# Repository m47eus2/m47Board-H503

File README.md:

# m47Board-H503

## Custom PCB designed for STM32H503
- STM32C031C6T6 MCU
- USB-C port with ESD protection
- SWD and DFU programming interfaces
- Goldpin headers for all GPIO pins
- User Button and User Led
- RST and BOOT0 buttons
- TLV1117LV33DCYR 3.3V 1A LDO

## PCB Renders

## Schematic

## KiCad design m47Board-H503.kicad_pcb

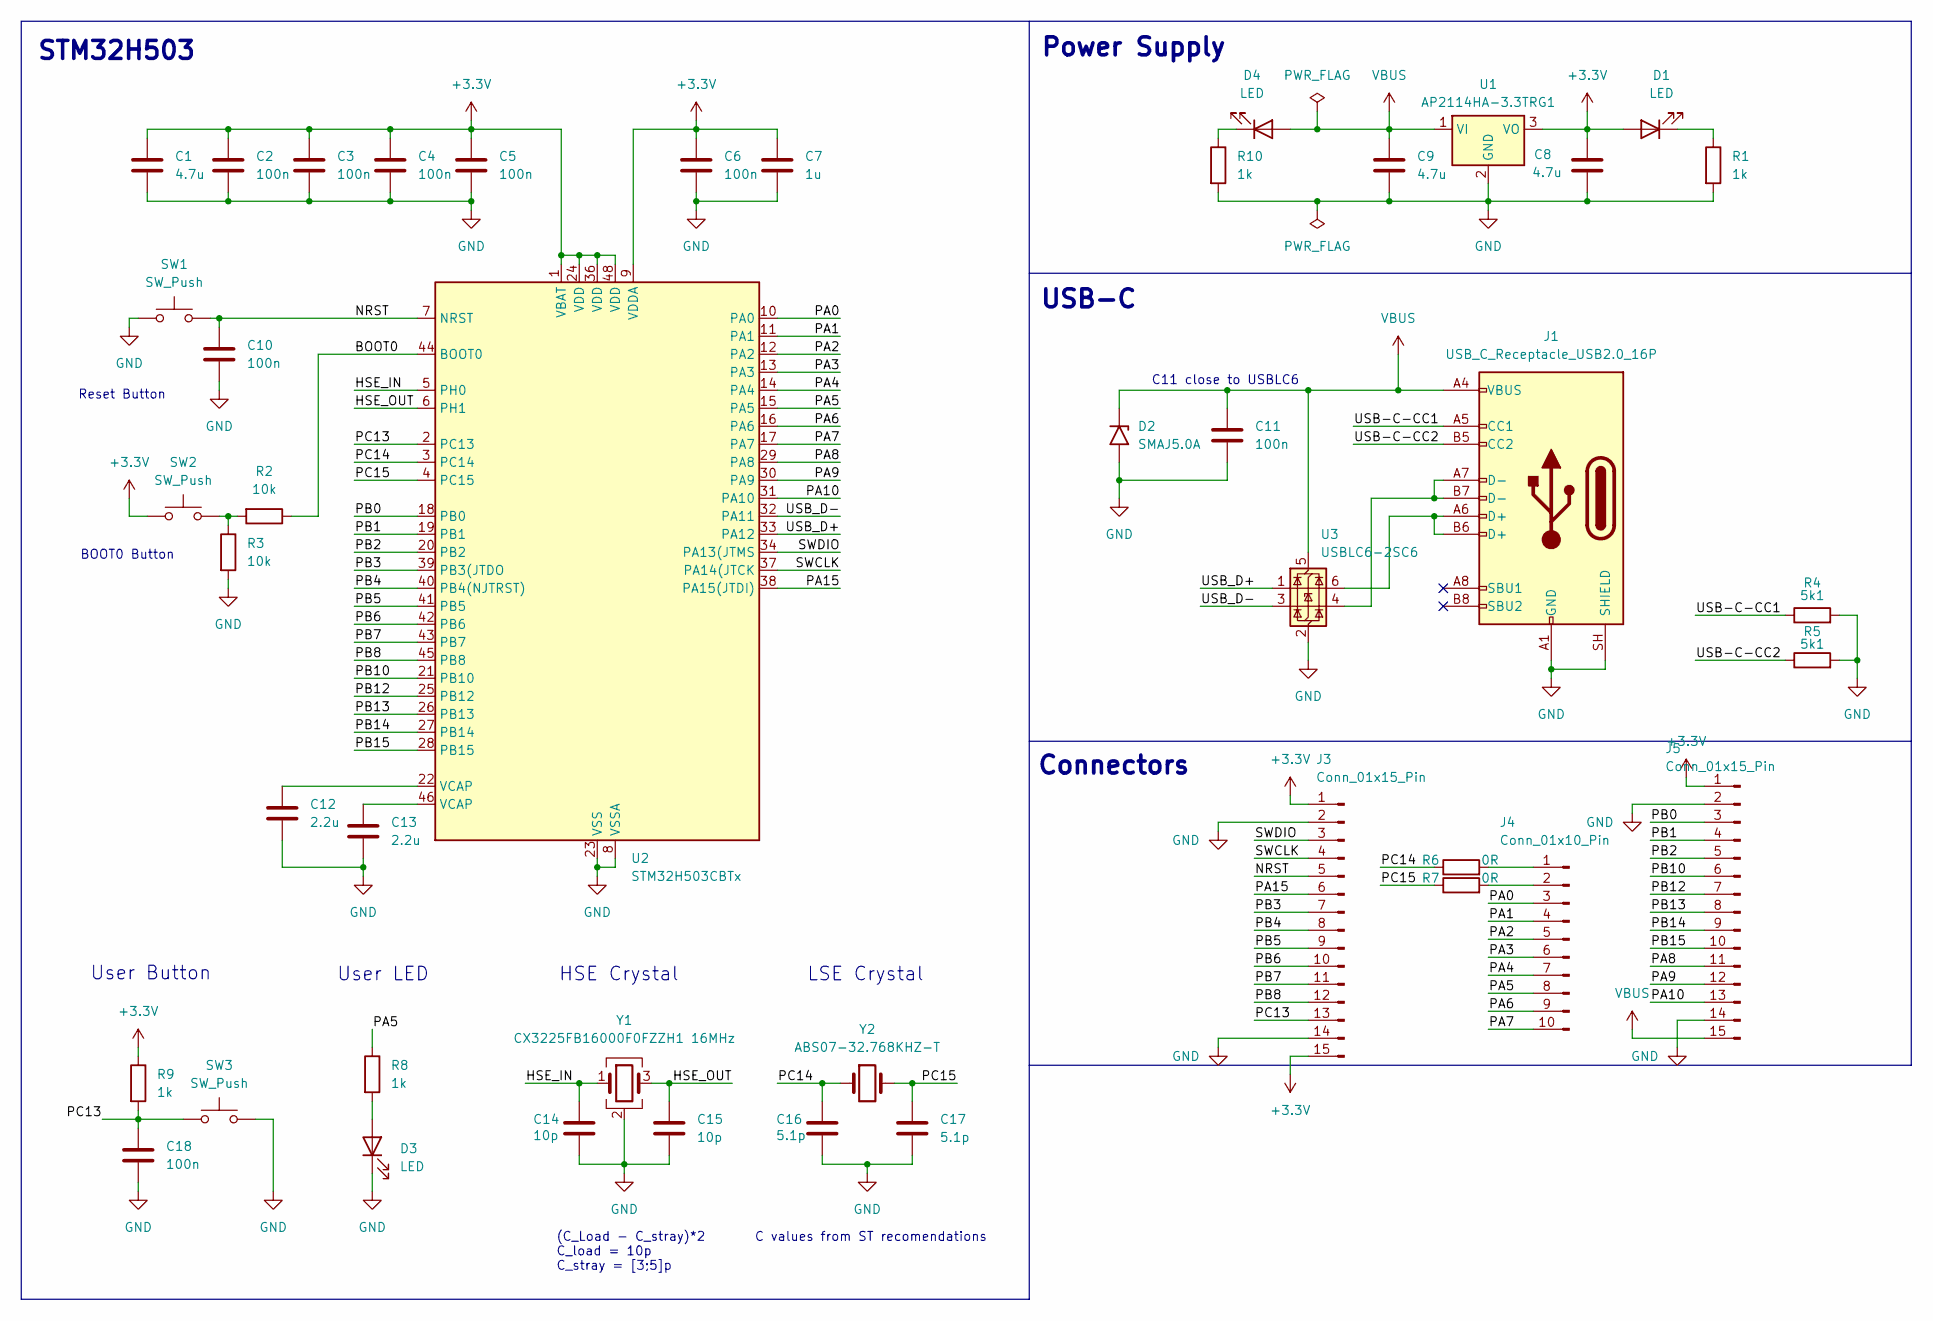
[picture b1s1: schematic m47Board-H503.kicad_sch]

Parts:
C1, C8, C9: 4.7u; C_0805_2012Metric_Pad1.18x1.45mm_HandSolder
C2, C3, C4, C5, C6, C10, C11, C18: 100n; C_0402_1005Metric_Pad0.74x0.62mm_HandSolder
C7: 1u; C_0603_1608Metric_Pad1.08x0.95mm_HandSolder
C12, C13: 2.2u; C_0603_1608Metric_Pad1.08x0.95mm_HandSolder
C14, C15: 10p; C_0402_1005Metric_Pad0.74x0.62mm_HandSolder
C16, C17: 5.1p; C_0402_1005Metric_Pad0.74x0.62mm_HandSolder
D1, D3, D4: LED; LED_0805_2012Metric_Pad1.15x1.40mm_HandSolder
D2: SMAJ5.0A; D_SMA
J1: USB_C_Receptacle_USB2.0_16P; USB_C_Receptacle_GCT_USB4105-xx-A_16P_TopMnt_Horizontal
J3, J5: Conn_01x15_Pin; PinHeader_1x15_P2.54mm_Vertical
J4: Conn_01x10_Pin; PinHeader_1x10_P2.54mm_Vertical
R1, R8, R9, R10: 1k; R_0402_1005Metric_Pad0.72x0.64mm_HandSolder
R2, R3: 10k; R_0402_1005Metric_Pad0.72x0.64mm_HandSolder
R4, R5: 5k1; R_0402_1005Metric_Pad0.72x0.64mm_HandSolder
R6, R7: 0R; R_0402_1005Metric_Pad0.72x0.64mm_HandSolder
SW1, SW2, SW3: SW_Push; SW_Push_1P1T_NO_E-Switch_TL3301NxxxxxG
U1: AP2114HA-3.3TRG1; SOT-223-3_TabPin2
U2: STM32H503CBTx; LQFP-48_7x7mm_P0.5mm
U3: USBLC6-2SC6; SOT-23-6
Y1: CX3225FB16000F0FZZH1 16MHz; Crystal_SMD_3225-4Pin_3.2x2.5mm
Y2: ABS07-32.768KHZ-T; Crystal_SMD_3215-2Pin_3.2x1.5mm

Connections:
+3.3V: C1.1, C2.1, C3.1, C4.1, C5.1, C6.1, C7.1, C8.1, D1.2 (A), J3.1, J3.15, J5.1, R9.1, SW2.1, U1.3 (VO), U2.1 (VBAT), U2.9 (VDDA), U2.24 (VDD), U2.36 (VDD), U2.48 (VDD)
/BOOT0: R2.1, U2.44 (BOOT0)
/HSE_IN: C14.1, U2.5 (PH0), Y1.1
/HSE_OUT: C15.1, U2.6 (PH1), Y1.3
/NRST: C10.1, J3.5, SW1.2, U2.7 (NRST)
/PA0: J4.3, U2.10 (PA0)
/PA1: J4.4, U2.11 (PA1)
/PA2: J4.5, U2.12 (PA2)
/PA3: J4.6, U2.13 (PA3)
/PA4: J4.7, U2.14 (PA4)
/PA5: J4.8, R8.1, U2.15 (PA5)
/PA6: J4.9, U2.16 (PA6)
/PA7: J4.10, U2.17 (PA7)
/PA8: J5.11, U2.29 (PA8)
/PA9: J5.12, U2.30 (PA9)
/PA10: J5.13, U2.31 (PA10)
/PA15: J3.6, U2.38 (PA15(JTDI))
/PB0: J5.3, U2.18 (PB0)
/PB1: J5.4, U2.19 (PB1)
/PB2: J5.5, U2.20 (PB2)
/PB3: J3.7, U2.39 (PB3(JTDO)
/PB4: J3.8, U2.40 (PB4(NJTRST))
/PB5: J3.9, U2.41 (PB5)
/PB6: J3.10, U2.42 (PB6)
/PB7: J3.11, U2.43 (PB7)
/PB8: J3.12, U2.45 (PB8)
/PB10: J5.6, U2.21 (PB10)
/PB12: J5.7, U2.25 (PB12)
/PB13: J5.8, U2.26 (PB13)
/PB14: J5.9, U2.27 (PB14)
/PB15: J5.10, U2.28 (PB15)
/PC13: C18.1, J3.13, R9.2, SW3.1, U2.2 (PC13)
/PC14: C16.1, R6.1, U2.3 (PC14), Y2.1
/PC15: C17.1, R7.1, U2.4 (PC15), Y2.2
/SWCLK: J3.4, U2.37 (PA14(JTCK)
/SWDIO: J3.3, U2.34 (PA13(JTMS)
/USB-C-CC1: J1.A5 (CC1), R4.1
/USB-C-CC2: J1.B5 (CC2), R5.1
/USB_D+: U2.33 (PA12), U3.1 (I/O1)
/USB_D-: U2.32 (PA11), U3.3 (I/O2)
GND: C1.2, C2.2, C3.2, C4.2, C5.2, C6.2, C7.2, C8.2, C9.2, C10.2, C11.2, C12.2, C13.2, C14.2, C15.2, C16.2, C17.2, C18.2, D2.2 (A2), D3.1 (K), J1.A1 (GND), J1.A12 (GND), J1.B1 (GND), J1.B12 (GND), J1.SH (SHIELD), J3.2, J3.14, J5.2, J5.14, R1.2, R3.2, R4.2, R5.2, R10.2, SW1.1, SW3.2, U1.2 (GND), U2.8 (VSSA), U2.23 (VSS), U2.35 (VSS), U2.47 (VSS), U3.2 (GND), Y1.2 (G), Y1.4 (G)
unnamed: C12.1, U2.22 (VCAP)
unnamed: C13.1, U2.46 (VCAP)
unnamed: D1.1 (K), R1.1
unnamed: D3.2 (A), R8.2
unnamed: D4.1 (K), R10.1
unnamed: J1.A6 (D+), J1.B6 (D+), U3.6 (I/O1)
unnamed: J1.A7 (D-), J1.B7 (D-), U3.4 (I/O2)
unnamed: J4.1, R6.2
unnamed: J4.2, R7.2
unnamed: R2.2, R3.1, SW2.2
VBUS: C9.1, C11.1, D2.1 (A1), D4.2 (A), J1.A4 (VBUS), J1.A9 (VBUS), J1.B4 (VBUS), J1.B9 (VBUS), J5.15, U1.1 (VI), U3.5 (VBUS)

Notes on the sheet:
USB-C
LSE Crystal
Reset Button
User Button
C values from ST recomendations
BOOT0 Button
Power Supply
C11 close to USBLC6
(C_Load - C_stray)*2 C_load = 10p C_stray = [3;5]p
STM32H503
User LED
Connectors
HSE Crystal

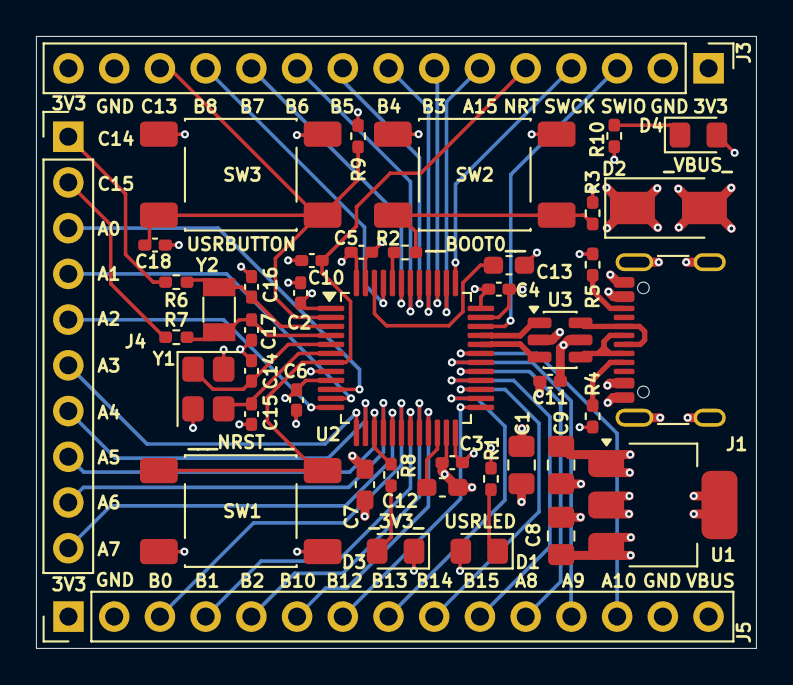
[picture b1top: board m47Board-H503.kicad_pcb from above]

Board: 4 copper layers, 40.0 x 34.0 mm, 44 parts (0 on the bottom side), 52 nets.

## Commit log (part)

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2026-06-28 Part of schematic and pinout for m47Board-H503
2026-06-29 Update m47Board-H503 schematic
